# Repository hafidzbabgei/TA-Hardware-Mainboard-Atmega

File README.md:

# TA-Hardware-Mainboard-Atmega
Control motor DC for CNC

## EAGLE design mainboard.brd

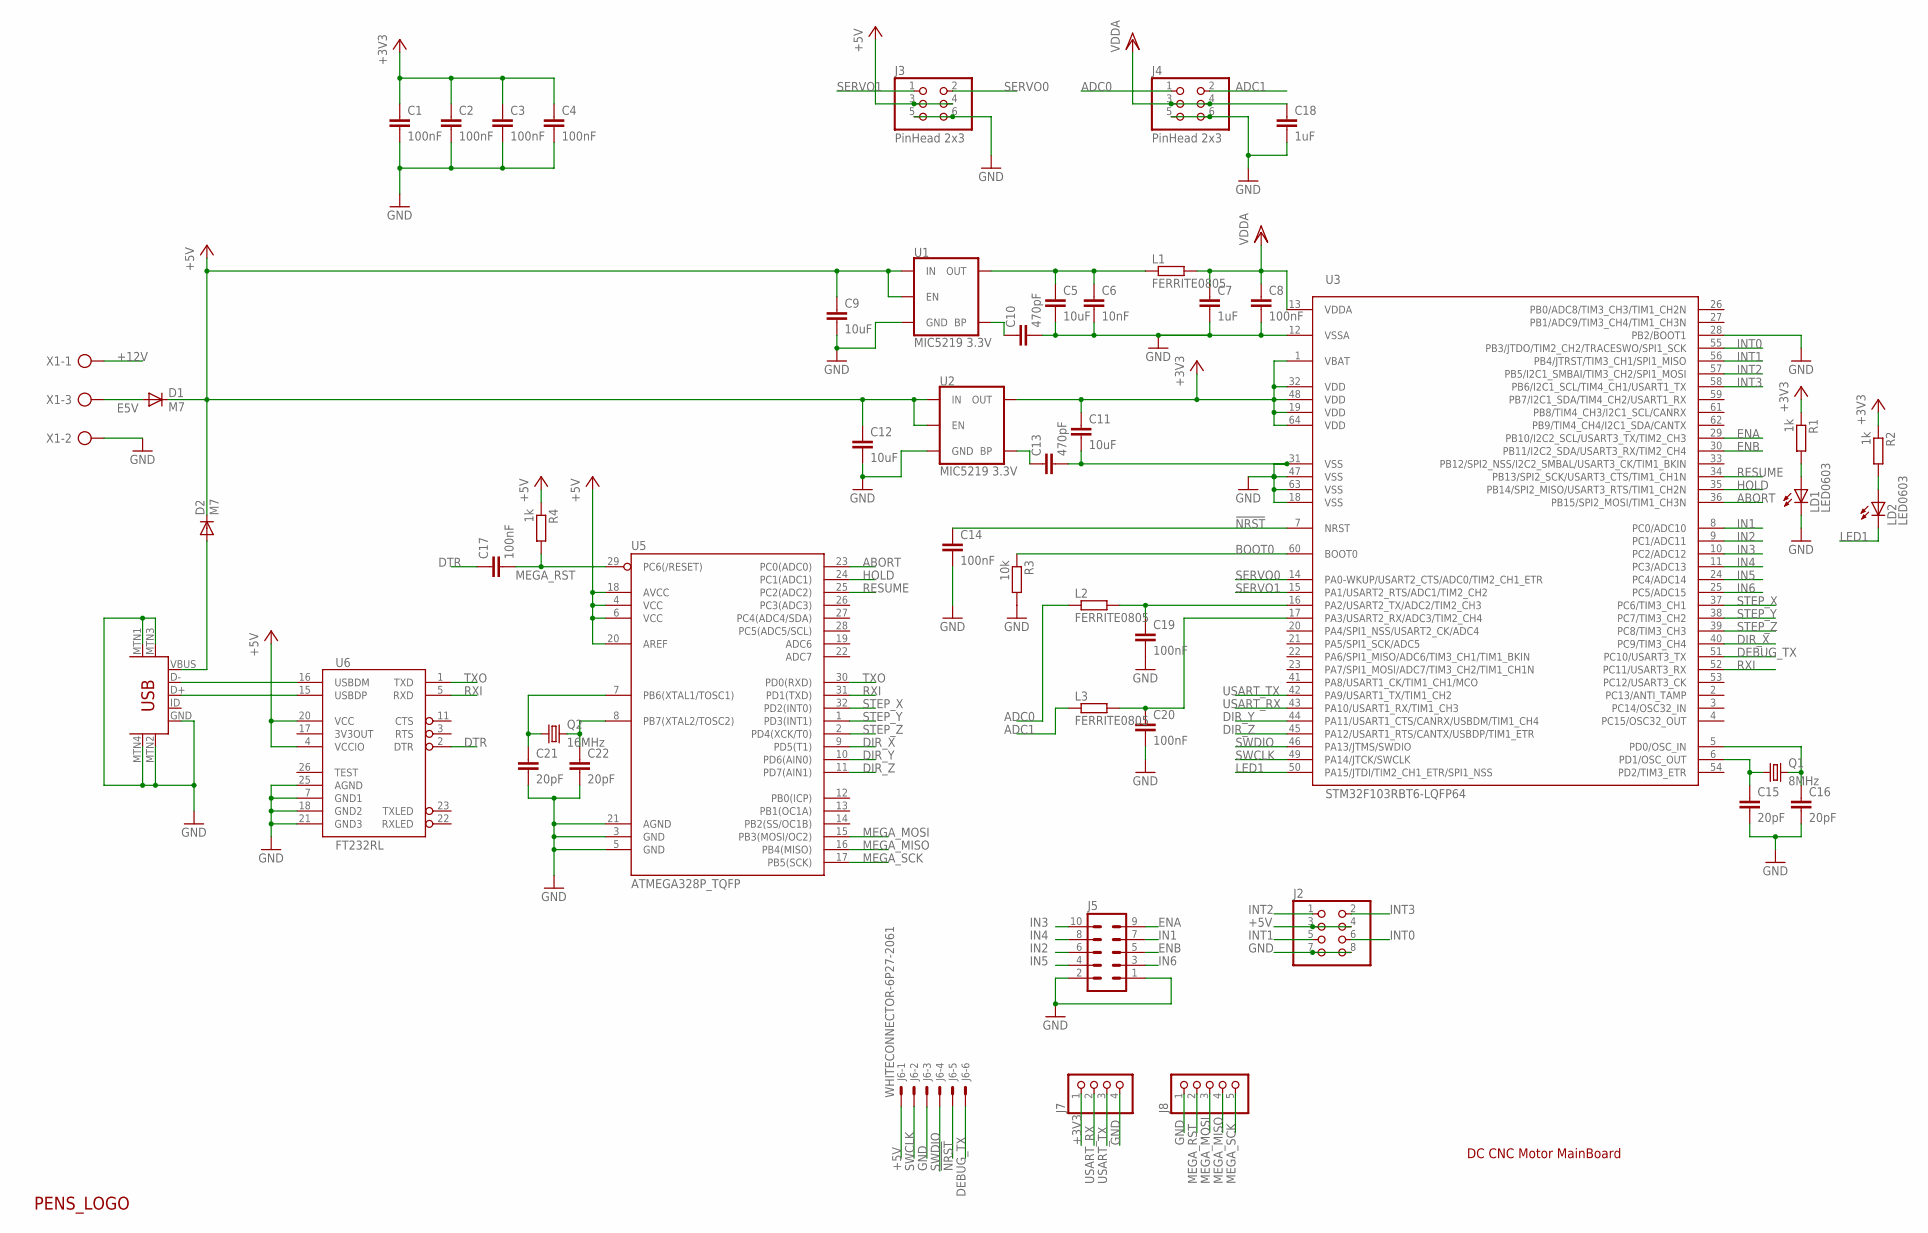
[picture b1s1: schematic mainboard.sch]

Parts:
C1, C2, C3, C4, C8, C14, C17, C19, C20: 100nF; 0603_MP
C5, C9, C11, C12: 10uF; 0805_MP
C6: 10nF; 0603_MP
C7, C18: 1uF; 0603_MP
C10, C13: 470pF; 0603_MP
C15, C16, C21, C22: 20pF; 0603_MP
D1, D2: M7; DIODE_SMA_ALT
J1: USB-MINI-B-5PIN; USB-MINIB
J2: PINHD-2X4/90; 2X04/90
J3, J4: PinHead 2x3; 2X03/90
J5: ML10
J6: WHITECONNECTOR-6P27-2061; 6410-06
J7: PINHD-1X4; 1X04
J8: HEADER-1X51.27MM; 1X05_1.27MM
L1, L2, L3: FERRITE0805; R0805
LD1, LD2: LED0603
LOGO1: PENS_LOGO
Q1: 8MHz; CRYSTAL-DIP
Q2: 16MHz; CRYSTAL-DIP
R1, R2, R4: 1k; 0603_MP
R3: 10k; 0603_MP
U1, U2: MIC5219 3.3V; SOT23-5
U3: STM32F103RBT6-LQFP64; LPTQFP64
U5: ATMEGA328P_TQFP; TQFP32-08
U6: FT232RL; SSOP28DB
X1: AK300/3

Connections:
!NRST: C14.1, J6.5, U3.7 (NRST)
+3V3: C1.1, C2.1, C3.1, C4.1, C11.1, J7.1, R1.1, R2.1, U2.5 (OUT), U3.1 (VBAT), U3.19 (VDD), U3.32 (VDD), U3.48 (VDD), U3.64 (VDD)
+5V: C9.1, C12.1, D1.C, D2.C, J2.3, J2.4, J3.3, J3.4, J6.1, R4.1, U1.1 (IN), U1.3 (EN), U2.1 (IN), U2.3 (EN), U5.4 (VCC), U5.6 (VCC), U5.18 (AVCC), U5.20 (AREF), U6.4 (VCCIO), U6.20 (VCC)
+12V: X1.1
ABORT: U3.36 (PB15/SPI2_MOSI/TIM1_CH3N), U5.23 (PC0(ADC0))
ADC0: J4.1, L2.1
ADC1: J4.2, L3.1
BOOT0: R3.1, U3.60 (BOOT0)
DEBUG_TX: J6.6, U3.51 (PC10/USART3_TX)
DIR_X: U3.40 (PC9/TIM3_CH4), U5.9 (PD5(T1))
DIR_Y: U3.44 (PA11/USART1_CTS/CANRX/USBDM/TIM1_CH4), U5.10 (PD6(AIN0))
DIR_Z: U3.45 (PA12/USART1_RTS/CANTX/USBDP/TIM1_ETR), U5.11 (PD7(AIN1))
DTR: C17.1, U6.2 (DTR)
E5V: D1.A, X1.3
ENA: J5.9, U3.29 (PB10/I2C2_SCL/USART3_TX/TIM2_CH3)
ENB: J5.5, U3.30 (PB11/I2C2_SDA/USART3_RX/TIM2_CH4)
GND: C1.2, C2.2, C3.2, C4.2, C5.2, C6.2, C7.2, C8.2, C9.2, C10.2, C11.2, C12.2, C13.2, C14.2, C15.2, C16.2, C18.2, C19.2, C20.2, C21.2, C22.2, J1.GND, J1.MTN1 (MTN2), J1.MTN2 (MTN3), J1.MTN3 (MTN1), J1.MTN4, J2.7, J2.8, J3.5, J3.6, J4.5, J4.6, J5.1, J5.2, J6.3, J7.4, J8.1, LD1.C, R3.2, U1.2 (GND), U2.2 (GND), U3.12 (VSSA), U3.18 (VSS), U3.28 (PB2/BOOT1), U3.31 (VSS), U3.47 (VSS), U3.63 (VSS), U5.3 (GND), U5.5 (GND), U5.21 (AGND), U6.7 (GND1), U6.18 (GND2), U6.21 (GND3), U6.25 (AGND), X1.2
HOLD: U3.35 (PB14/SPI2_MISO/USART3_RTS/TIM1_CH2N), U5.24 (PC1(ADC1))
IN1: J5.7, U3.8 (PC0/ADC10)
IN2: J5.6, U3.9 (PC1/ADC11)
IN3: J5.10, U3.10 (PC2/ADC12)
IN4: J5.8, U3.11 (PC3/ADC13)
IN5: J5.4, U3.24 (PC4/ADC14)
IN6: J5.3, U3.25 (PC5/ADC15)
INT0: J2.6, U3.55 (PB3/JTDO/TIM2_CH2/TRACESWO/SPI1_SCK)
INT1: J2.5, U3.56 (PB4/JTRST/TIM3_CH1/SPI1_MISO)
INT2: J2.1, U3.57 (PB5/I2C1_SMBAI/TIM3_CH2/SPI1_MOSI)
INT3: J2.2, U3.58 (PB6/I2C1_SCL/TIM4_CH1/USART1_TX)
LED1: LD2.C, U3.50 (PA15/JTDI/TIM2_CH1_ETR/SPI1_NSS)
MEGA_MISO: J8.4, U5.16 (PB4(MISO))
MEGA_MOSI: J8.3, U5.15 (PB3(MOSI/OC2))
MEGA_RST: C17.2, J8.2, R4.2, U5.29 (PC6(/RESET))
MEGA_SCK: J8.5, U5.17 (PB5(SCK))
unnamed: J1.D+, U6.15 (USBDP)
unnamed: J1.D-, U6.16 (USBDM)
unnamed: C19.1, L2.2, U3.16 (PA2/USART2_TX/ADC2/TIM2_CH3)
unnamed: C20.1, L3.2, U3.17 (PA3/USART2_RX/ADC3/TIM2_CH4)
unnamed: C15.1, Q1.1, U3.6 (PD1/OSC_OUT)
unnamed: D2.A, J1.VBUS
unnamed: C5.1, C6.1, L1.1, U1.5 (OUT)
unnamed: C21.1, Q2.1, U5.7 (PB6(XTAL1/TOSC1))
unnamed: C16.1, Q1.2, U3.5 (PD0/OSC_IN)
unnamed: C10.1, U1.4 (BP)
unnamed: C22.1, Q2.2, U5.8 (PB7(XTAL2/TOSC2))
unnamed: LD1.A, R1.2
unnamed: LD2.A, R2.2
unnamed: C13.1, U2.4 (BP)
RESUME: U3.34 (PB13/SPI2_SCK/USART3_CTS/TIM1_CH1N), U5.25 (PC2(ADC2))
RXI: U3.52 (PC11/USART3_RX), U5.31 (PD1(TXD)), U6.5 (RXD)
SERVO0: J3.2, U3.14 (PA0-WKUP/USART2_CTS/ADC0/TIM2_CH1_ETR)
SERVO1: J3.1, U3.15 (PA1/USART2_RTS/ADC1/TIM2_CH2)
STEP_X: U3.37 (PC6/TIM3_CH1), U5.32 (PD2(INT0))
STEP_Y: U3.38 (PC7/TIM3_CH2), U5.1 (PD3(INT1))
STEP_Z: U3.39 (PC8/TIM3_CH3), U5.2 (PD4(XCK/T0))
SWCLK: J6.2, U3.49 (PA14/JTCK/SWCLK)
SWDIO: J6.4, U3.46 (PA13/JTMS/SWDIO)
TXO: U5.30 (PD0(RXD)), U6.1 (TXD)
USART_RX: J7.2, U3.43 (PA10/USART1_RX/TIM1_CH3)
USART_TX: J7.3, U3.42 (PA9/USART1_TX/TIM1_CH2)
VDDA: C7.1, C8.1, C18.1, J4.3, J4.4, L1.2, U3.13 (VDDA)

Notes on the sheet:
DC CNC Motor MainBoard

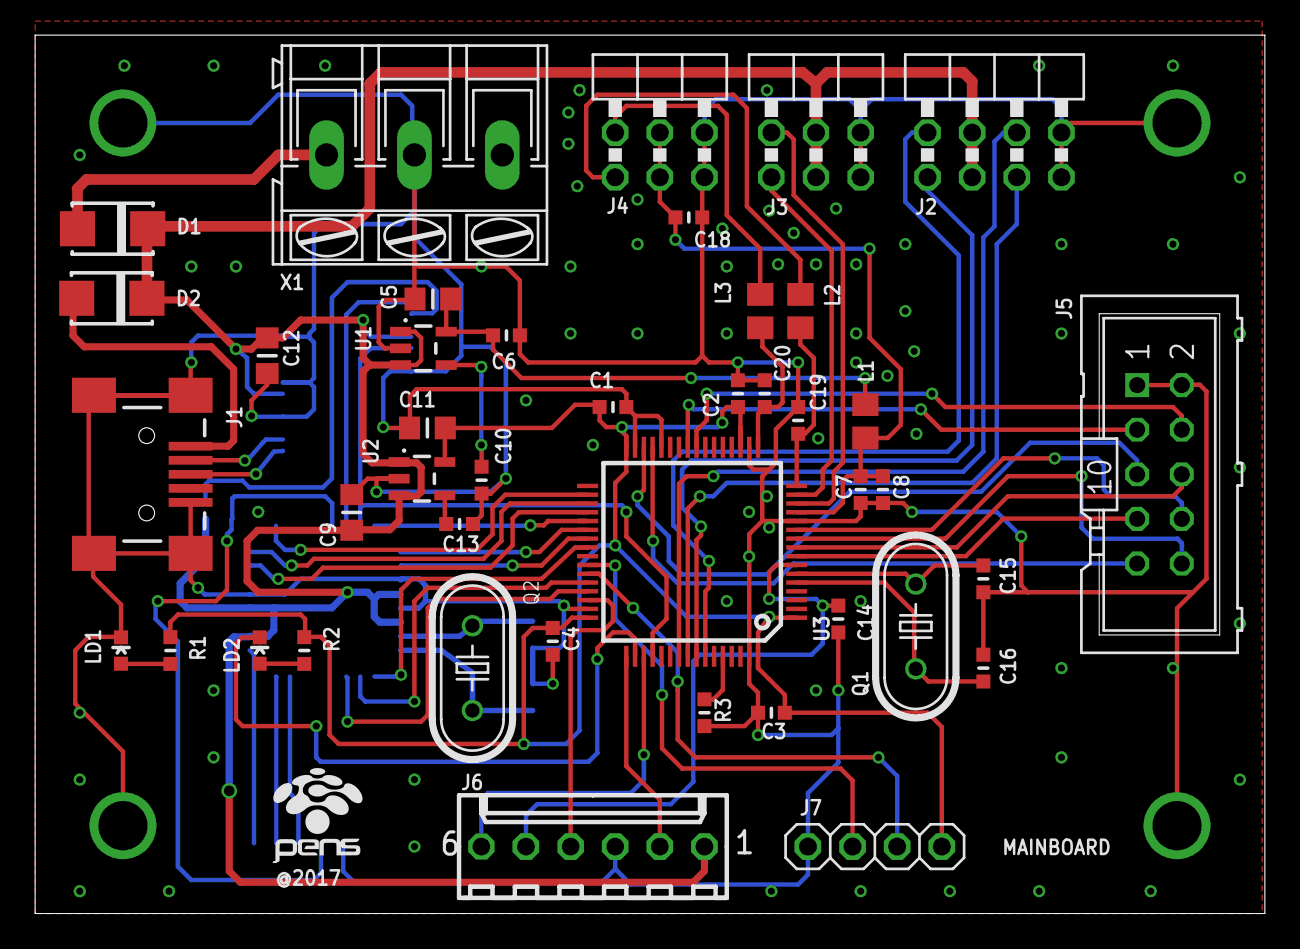
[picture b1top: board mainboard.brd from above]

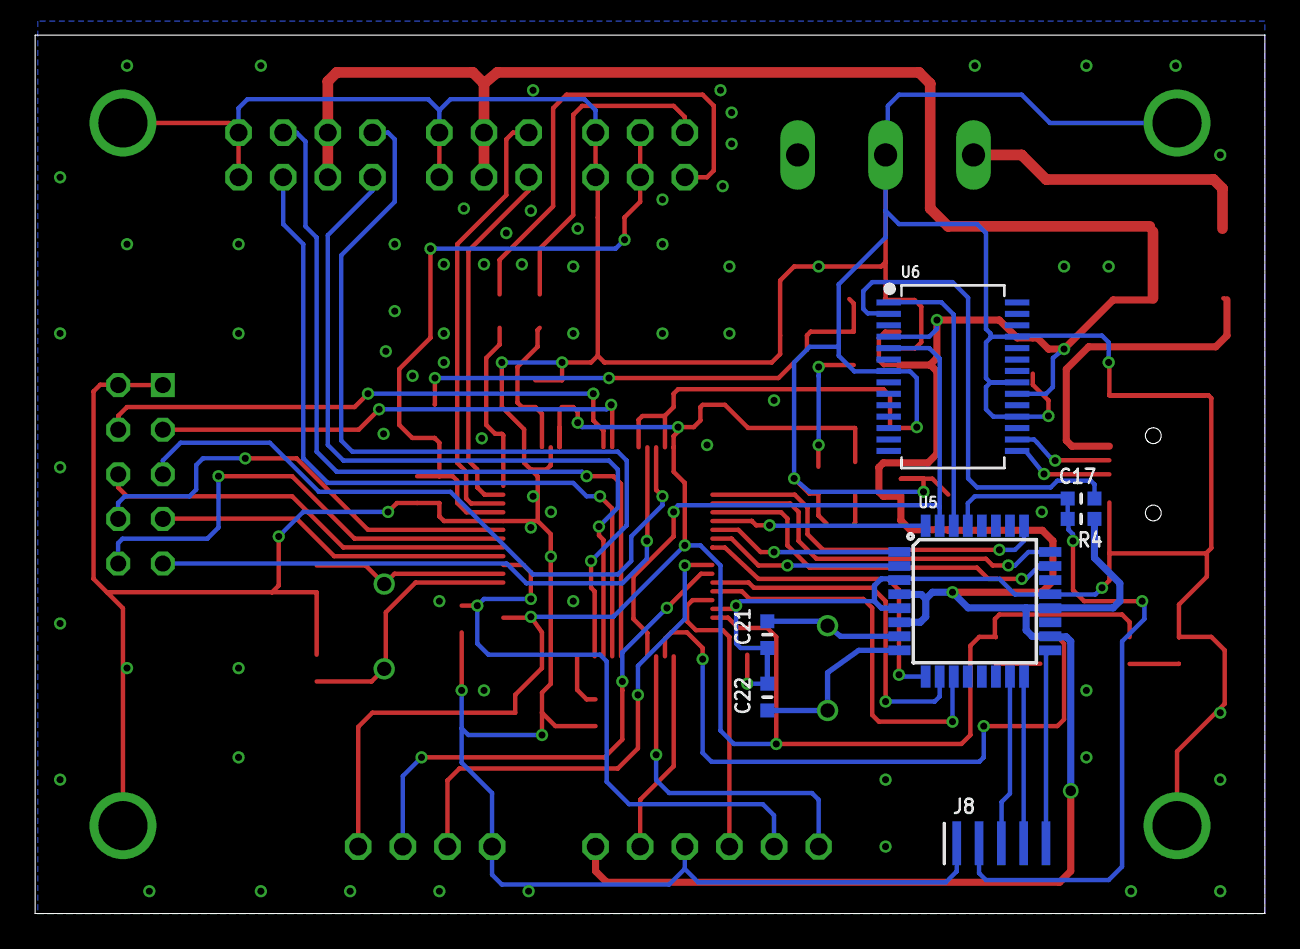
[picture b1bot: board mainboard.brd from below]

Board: 2 copper layers, 70.0 x 50.0 mm, 50 parts (7 on the bottom side), 59 nets.

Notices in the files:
parts and their libraries:
SparkFun-IC-Power: Licensing: Creative Commons ShareAlike 4.0 International - https://creativecommons.org/licenses/by-sa/4.0
microbuilder: This work is placed in the public domain, and may be freely used for commercial and non-commercial work with the following conditions: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
